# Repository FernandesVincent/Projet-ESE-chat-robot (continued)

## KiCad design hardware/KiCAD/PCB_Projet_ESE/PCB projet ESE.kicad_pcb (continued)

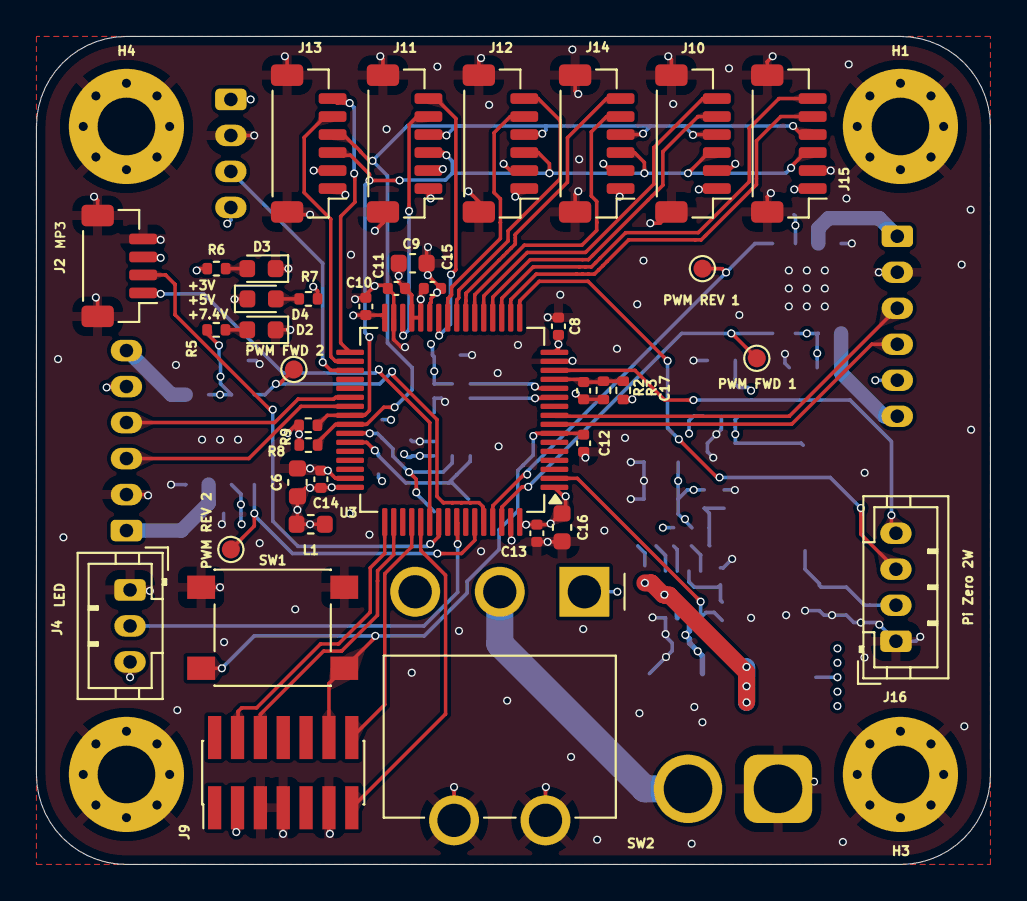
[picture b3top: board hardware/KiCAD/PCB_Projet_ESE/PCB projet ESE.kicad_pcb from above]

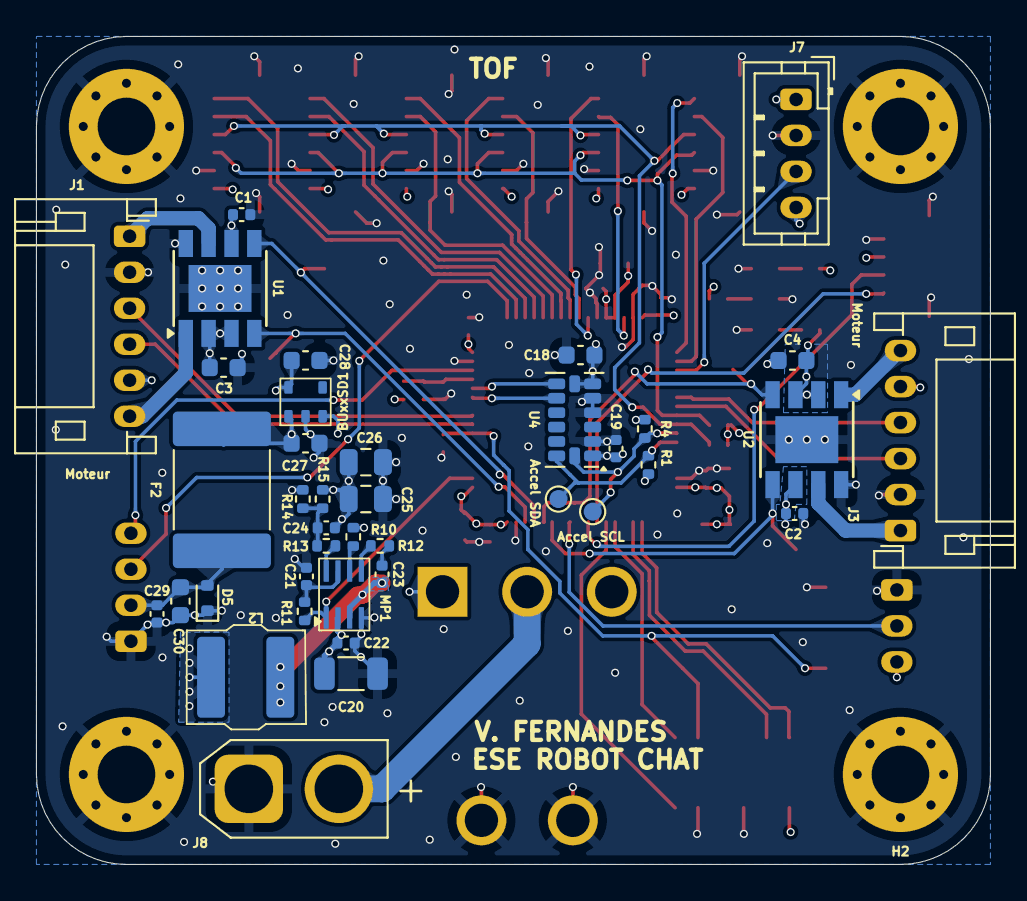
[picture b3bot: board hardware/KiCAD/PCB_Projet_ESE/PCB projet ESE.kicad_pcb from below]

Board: 4 copper layers, 53.0 x 46.0 mm, 82 parts (40 on the bottom side), 59 nets.

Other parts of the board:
Accel SCL: TestPoint; TestPoint_Pad_D1.0mm
Accel SDA: TestPoint; TestPoint_Pad_D1.0mm
PWM FWD 1, PWM FWD 2: TestPoint; TestPoint_Pad_D1.0mm
PWM REV 1, PWM REV 2: TestPoint; TestPoint_Pad_D1.0mm

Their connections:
Accel SCL: Accel SCL.1; also elsewhere on the board
Accel SDA: Accel SDA.1; also elsewhere on the board
PWM FWD 1: PWM FWD 1.1; also elsewhere on the board
PWM FWD 2: PWM FWD 2.1; also elsewhere on the board
PWM REV 1: PWM REV 1.1; also elsewhere on the board
PWM REV 2: PWM REV 2.1; also elsewhere on the board

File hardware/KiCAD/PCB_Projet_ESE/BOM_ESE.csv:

'Reference';'Qty';'Value';'Footprint'
'BUxxSD1';'1';'~';'Régu:SSOP5_BUxxSD5'
'C1,C2,C8,C10,C11,C12,C13,C14,C17,C19,C21,C22,C23,C29';'14';'100n';'Capacitor_SMD:C_0402_1005Metric'
'C3,C4,C6';'3';'4u7';'Capacitor_SMD:C_0603_1608Metric'
'C9,C16,C18,C27,C28';'5';'1u';'Capacitor_SMD:C_0603_1608Metric'
'C15';'1';'10n';'Capacitor_SMD:C_0402_1005Metric'
'C20';'1';'22u';'Capacitor_SMD:C_1206_3216Metric'
'C24';'1';'15p';'Capacitor_SMD:C_0402_1005Metric'
'C25,C26';'2';'22u';'Capacitor_SMD:C_0805_2012Metric'
'C30';'1';'10u';'Capacitor_SMD:C_0603_1608Metric'
'D2,D3,D4';'3';'LED';'LED_SMD:LED_0603_1608Metric'
'D5';'1';'D_TVS_Small';'Diode_SMD:D_SOD-523'
'F2';'1';'1A';'Fuse:Fuse_2920_7451Metric'
'H1,H2,H3,H4';'4';'MountingHole_Pad';'MountingHole:MountingHole_3.2mm_M3_Pad_Via'
'J1,J3';'2';'Conn_01x06';'Connector_JST:JST_PH_S6B-PH-K_1x06_P2.00mm_Horizontal'
'J2';'1';'Conn_01x04';'Connector_JST:JST_SH_BM04B-SRSS-TB_1x04-1MP_P1.00mm_Vertical'
'J4';'1';'Conn_01x03';'Connector_JST:JST_PH_B3B-PH-K_1x03_P2.00mm_Vertical'
'J7,J16';'2';'Conn_01x04';'Connector_JST:JST_PH_B4B-PH-K_1x04_P2.00mm_Vertical'
'J8';'1';'Conn_01x02';'Connector_AMASS:AMASS_XT30U-M_1x02_P5.0mm_Vertical'
'J9';'1';'Conn_ST_STDC14';'Connector_PinHeader_1.27mm:PinHeader_2x07_P1.27mm_Vertical_SMD'
'J10,J11,J12,J13,J14,J15';'6';'Conn_01x06';'Connector_JST:JST_SH_BM06B-SRSS-TB_1x06-1MP_P1.00mm_Vertical'
'L1';'1';'39n';'Inductor_SMD:L_0603_1608Metric'
'L2';'1';'4u7';'Régu:74404054068'
'MP1';'1';'~';'Régu:TSOT23-8'
'R1,R4,R8,R9';'4';'1k';'Resistor_SMD:R_0402_1005Metric'
'R2';'1';'20k';'Resistor_SMD:R_0402_1005Metric'
'R3';'1';'5k6';'Resistor_SMD:R_0402_1005Metric'
'R5';'1';'2k9';'Resistor_SMD:R_0402_1005Metric'
'R6';'1';'1k65';'Resistor_SMD:R_0402_1005Metric'
'R7';'1';'800';'Resistor_SMD:R_0402_1005Metric'
'R10,R11';'2';'100k';'Resistor_SMD:R_0402_1005Metric'
'R12';'1';'20';'Resistor_SMD:R_0402_1005Metric'
'R13';'1';'16k';'Resistor_SMD:R_0402_1005Metric'
'R14';'1';'7k68';'Resistor_SMD:R_0402_1005Metric'
'R15';'1';'40k2';'Resistor_SMD:R_0402_1005Metric'
'SW1';'1';'SW_SPST';'Régu:SW_SPST'
'SW2';'1';'472121010111';'Régu:SW_Wurth_WS-TOTV_472123020421'
'TP1,TP2,TP3,TP4,TP5,TP6';'6';'TestPoint';'TestPoint:TestPoint_Pad_D1.0mm'
'U1,U2';'2';'ZXBM5210-SP';'Package_SO:Diodes_SO-8EP'
'U3';'1';'STM32G474RETx';'Package_QFP:LQFP-64_10x10mm_P0.5mm'
'U4';'1';'ADXL343';'Package_LGA:LGA-14_3x5mm_P0.8mm_LayoutBorder1x6y'

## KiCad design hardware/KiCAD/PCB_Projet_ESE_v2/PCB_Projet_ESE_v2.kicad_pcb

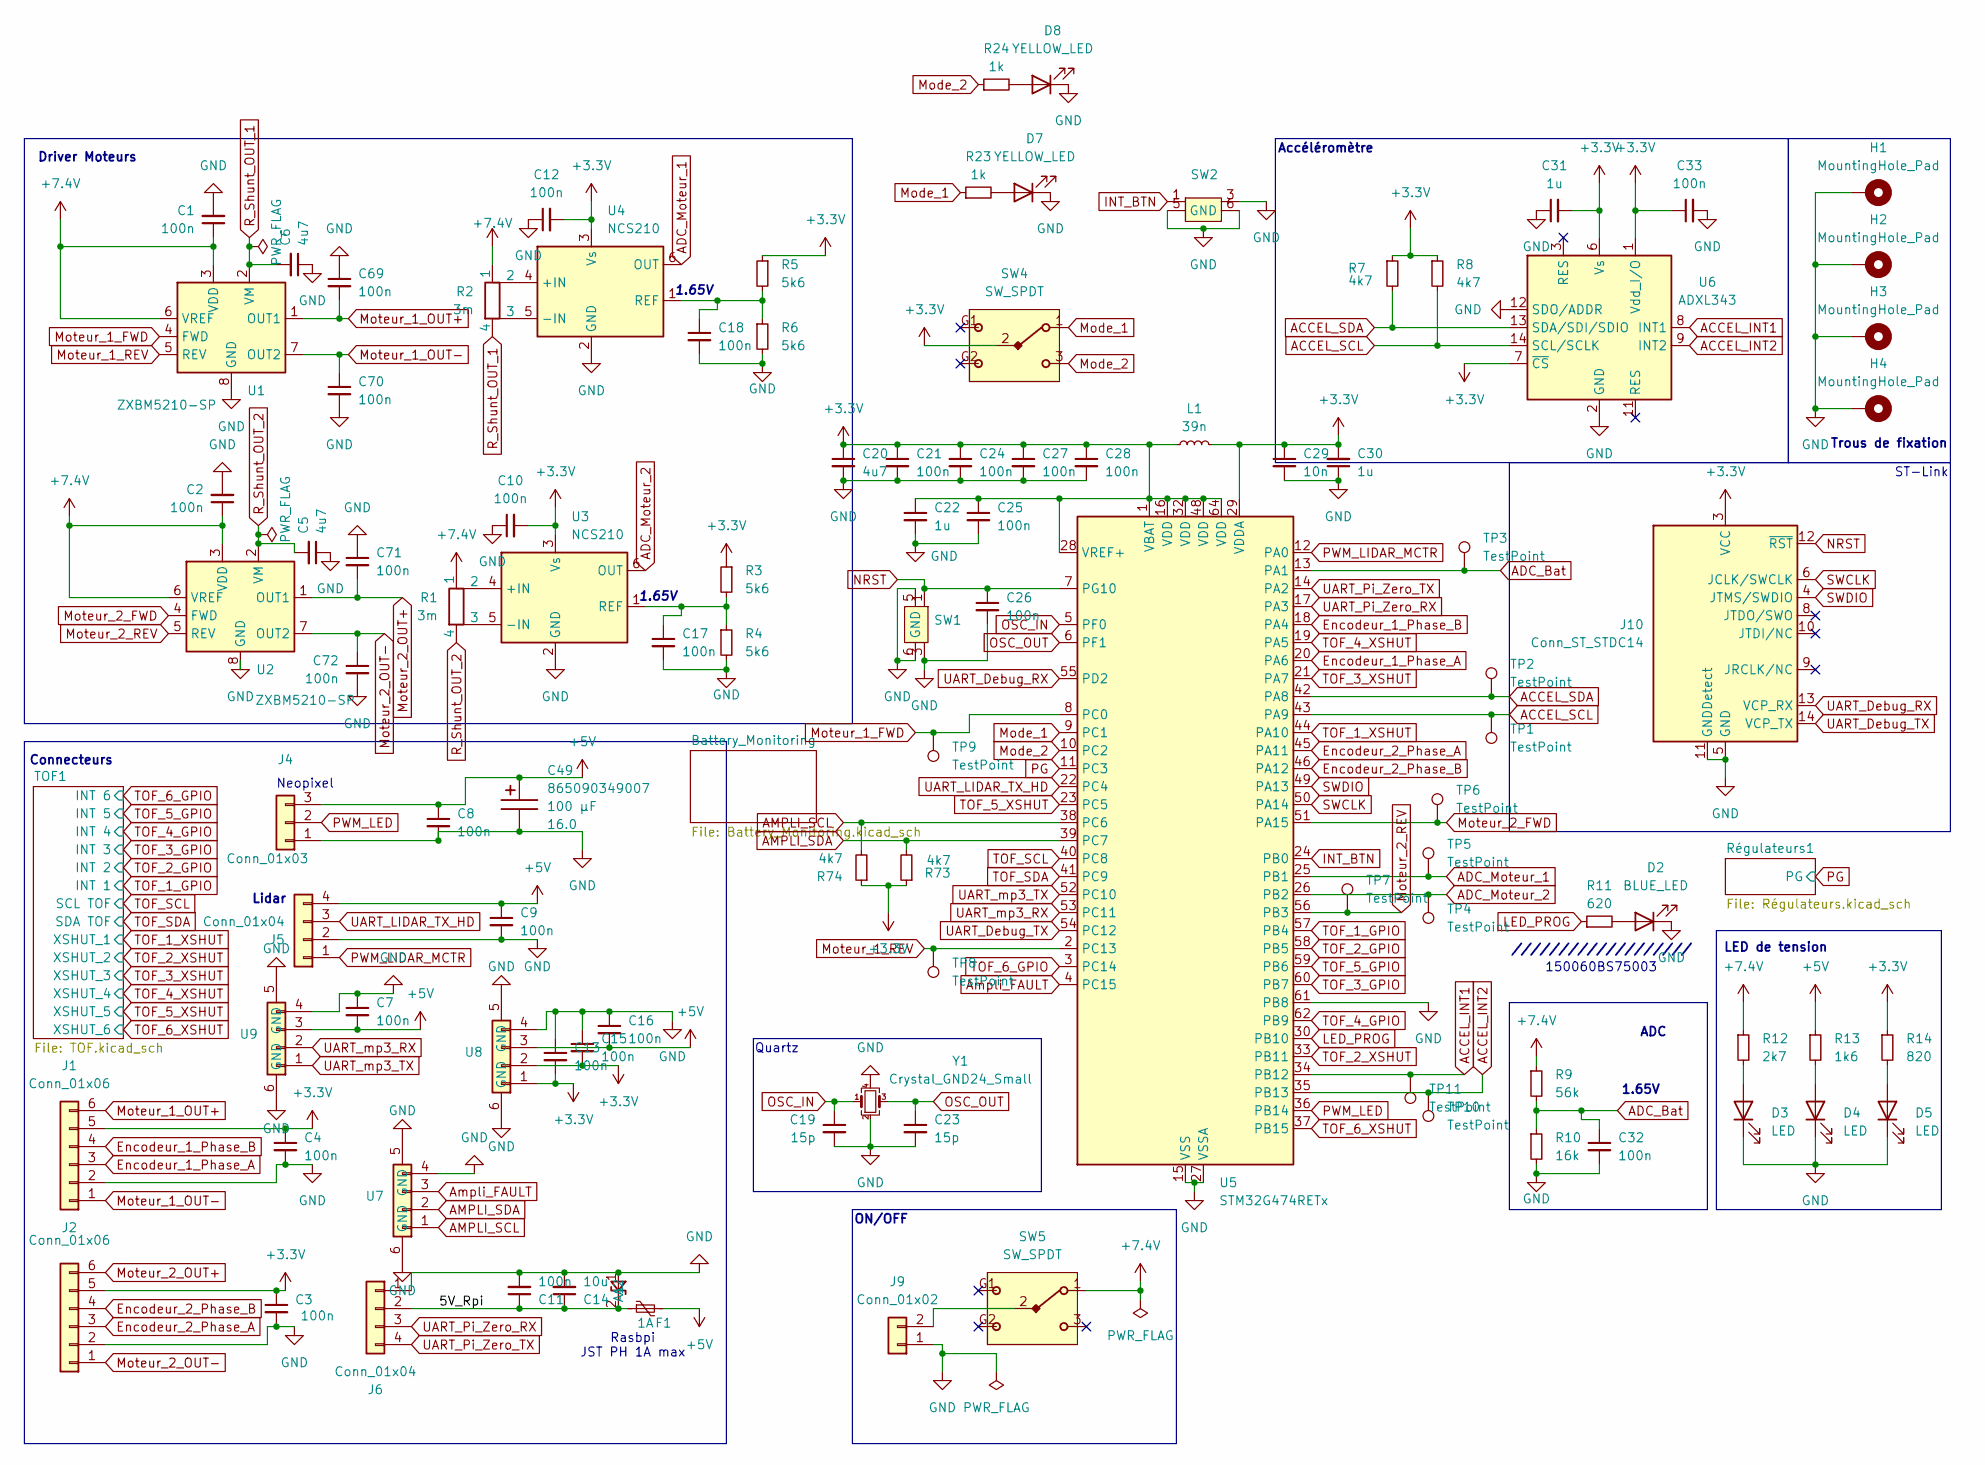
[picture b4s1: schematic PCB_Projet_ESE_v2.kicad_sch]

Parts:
C1, C2, C3, C4, C7, C8, C9, C10, C11, C12, C13, C15, C16, C17, C18, C21, C24, C25, C26, C27, C28, C32, C33, C69, C70, C71, C72: 100n; C_0402_1005Metric
C5, C6, C20: 4u7; C_0603_1608Metric
C14: 10u; C_0603_1608Metric
C19, C23: 15p; C_0603_1608Metric
C22, C30, C31: 1u; C_0402_1005Metric
C29: 10n; C_0402_1005Metric
C49: D8L6.5_865090349007; CP_Wurth_WCAP-ASLU-D8L6.5; Voltage 16.0; Part Number 865090349007
D2: BLUE_LED; LED_0603_1608Metric; MPN VLMB1501-GS08
D3, D4, D5: LED; LED_0603_1608Metric
D7, D8: YELLOW_LED; wurth_155060YS75300; MPN 155060YS75300
D20: D_SOD-523
F1: 1A; Fuse_2920_7451Metric; MPN 0ZAF0013FF28
H1, H2, H3, H4: MountingHole_Pad; Pad_traversant_M1
J1, J2: Conn_01x06; JST_PH_S6B-PH-K_1x06_P2.00mm_Horizontal
J4: Conn_01x03; JST_PH_B3B-PH-K_1x03_P2.00mm_Vertical
J5, J6: Conn_01x04; J_Wurth_WR-WTB_62000411722
J9: Conn_01x02; AMASS_XT30U-M_1x02_P5.0mm_Vertical
J10: Conn_ST_STDC14; PinHeader_2x07_P1.27mm_Vertical_SMD; MPN STLINK-V3MINIE
L1: 39n; L_0603_1608Metric
R1, R2: 3m; R_Shunt_Vishay_WSK2512_6332Metric_T2.21mm; MPN WSK25123L000DEA
R3, R4, R5, R6: 5k6; R_0402_1005Metric
R7, R8, R73, R74: 4k7; R_0402_1005Metric
R9: 56k; R_0402_1005Metric
R10: 16k; R_0402_1005Metric
R11: 620; R_0402_1005Metric
R12: 2k7; R_0402_1005Metric
R13: 1k6; R_0402_1005Metric
R14: 820; R_0402_1005Metric
R23, R24: 1k; R_0402_1005Metric
SW1, SW2: WS-TASV SMT Tact Switch 3.0 x 2.6 mm
SW4, SW5: SW_SPDT; SW_Wurth_WS-TOTV_472123020421; Part Number 472121010111
TP1, TP2, TP3, TP4, TP5, TP6, TP7, TP8, TP9, TP10, TP11: TestPoint; TestPoint_Pad_D1.0mm
U1, U2: ZXBM5210-SP; Diodes_SO-8EP; MPN ZXBM5210-SP-13
U3, U4: NCS210; SOT-363_SC-70-6
U5: STM32G474RETx; LQFP-64_10x10mm_P0.5mm
U6: ADXL343; LGA-14_3x5mm_P0.8mm_LayoutBorder1x6y; MPN ADXL343BCCZ-RL
U7, U8, U9: Wurth_Vertical_4_pos_0.8mm
Y1: Crystal_GND24_Small; Crystal_SMD_3225-4Pin_3.2x2.5mm; MPN Farnell : 2853935

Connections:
+3.3V: C3.1, C4.1, C10.2, C12.2, C13.2, C15.2, C20.1, C21.1, C22.1, C24.1, C25.1, C27.1, C28.1, C29.1, C30.2, C31.2, C33.1, J1.5, J2.5, J10.3 (VCC), L1.1, L1.2, R3.1, R5.1, R7.1, R8.1, R14.1, R73.1, R74.1, SW4.2, U3.3 (Vs), U4.3 (Vs), U5.1 (VBAT), U5.16 (VDD), U5.28 (VREF+), U5.29 (VDDA), U5.32 (VDD), U5.48 (VDD), U5.64 (VDD), U6.1 (Vdd_I/O), U6.6 (Vs), U6.7 (~CS), U8.1, U8.2; also elsewhere on the board
+5V: C7.2, C8.1, C9.1, C16.2, C49.1, F1.2, J4.3, J5.4, R13.1, U8.3, U9.3; also elsewhere on the board
+7.4V: C1.1, C2.1, R1.1, R2.1, R9.1, R12.1, SW5.1, U1.3 (VDD), U1.6 (VREF), U2.3 (VDD), U2.6 (VREF); also elsewhere on the board
/5V_Rpi: C11.1, C14.1, D20.2 (A2), F1.1, J6.2
ACCEL_INT1: TP11.1, U5.34 (PB12), U6.8 (INT1)
ACCEL_INT2: TP10.1, U5.35 (PB13), U6.9 (INT2)
ACCEL_SCL: R8.2, TP1.1, U5.43 (PA9), U6.14 (SCL/SCLK)
ACCEL_SDA: R7.2, TP2.1, U5.42 (PA8), U6.13 (SDA/SDI/SDIO)
ADC_Bat: C32.1, R9.2, R10.1, TP3.1, U5.13 (PA1)
ADC_Moteur_1: TP5.1, U4.6 (OUT), U5.25 (PB1)
ADC_Moteur_2: TP4.1, U3.6 (OUT), U5.26 (PB2)
AMPLI_SCL: R74.2, U5.38 (PC6), U7.1
AMPLI_SDA: R73.2, U5.39 (PC7), U7.2
Ampli_FAULT: U5.4 (PC15), U7.3
Encodeur_1_Phase_A: J1.3, U5.20 (PA6)
Encodeur_1_Phase_B: J1.4, U5.18 (PA4)
Encodeur_2_Phase_A: J2.3, U5.45 (PA11)
Encodeur_2_Phase_B: J2.4, U5.46 (PA12)
GND: C1.2, C2.2, C3.2, C4.2, C5.1, C6.1, C7.1, C8.2, C9.2, C10.1, C11.2, C12.1, C13.1, C14.2, C15.1, C16.1, C17.2, C18.2, C19.2, C20.2, C21.2, C22.2, C23.2, C24.2, C25.2, C26.2, C27.2, C28.2, C29.2, C30.1, C31.1, C32.2, C33.2, C49.2, C69.1, C70.2, C71.1, C72.2, D2.1 (K), D3.1 (K), D4.1 (K), D5.1 (K), D7.1 (K), D8.1 (K), D20.1 (A1), H1.1, H2.1, H3.1, H4.1, J1.2, J2.2, J4.1, J5.2, J6.1, J9.1, J10.5 (GND), J10.7 (GND), J10.11 (GNDDetect), R4.2, R6.2, R10.2, SW1.3, SW1.4, SW1.5, SW1.6 (GND), SW2.3, SW2.4, SW2.5, SW2.6 (GND), U1.8 (GND), U1.9 (GND), U2.8 (GND), U2.9 (GND), U3.2 (GND), U4.2 (GND), U5.15 (VSS), U5.27 (VSSA), U5.31 (VSS), U5.47 (VSS), U5.61 (PB8), U5.63 (VSS), U6.2 (GND), U6.4 (GND), U6.5 (GND), U6.12 (SDO/ADDR), U7.4, U7.5 (GND), U7.6 (GND), U8.4, U8.5 (GND), U8.6 (GND), U9.4, U9.5 (GND), U9.6 (GND), Y1.2, Y1.4; also elsewhere on the board
INT_BTN: SW2.1, SW2.2, U5.24 (PB0)
LED_PROG: R11.1, U5.30 (PB10)
Mode_1: R23.1, SW4.1, U5.9 (PC1)
Mode_2: R24.1, SW4.3, U5.10 (PC2)
Moteur_1_FWD: TP9.1, U1.4 (FWD), U5.8 (PC0)
Moteur_1_OUT+: C69.2, J1.6, U1.1 (OUT1)
Moteur_1_OUT-: C70.1, J1.1, U1.7 (OUT2)
Moteur_1_REV: TP8.1, U1.5 (REV), U5.2 (PC13)
Moteur_2_FWD: TP6.1, U2.4 (FWD), U5.51 (PA15)
Moteur_2_OUT+: C71.2, J2.6, U2.1 (OUT1)
Moteur_2_OUT-: C72.1, J2.1, U2.7 (OUT2)
Moteur_2_REV: TP7.1, U2.5 (REV), U5.56 (PB3)
NRST: C26.1, J10.12 (~RST), SW1.1, SW1.2, U5.7 (PG10)
unnamed: D2.2 (A), R11.2
unnamed: D3.2 (A), R12.2
unnamed: D4.2 (A), R13.2
unnamed: D5.2 (A), R14.2
unnamed: D7.2 (A), R23.2
unnamed: D8.2 (A), R24.2
unnamed: J9.2, SW5.2
unnamed: R1.2, U3.4 (+IN)
unnamed: R1.3, U3.5 (-IN)
unnamed: C17.1, R3.2, R4.1, U3.1 (REF)
unnamed: R2.2, U4.4 (+IN)
unnamed: R2.3, U4.5 (-IN)
unnamed: C18.1, R5.2, R6.1, U4.1 (REF)
OSC_IN: C19.1, U5.5 (PF0), Y1.1
OSC_OUT: C23.1, U5.6 (PF1), Y1.3
PG: U5.11 (PC3); also elsewhere on the board
PWM_LED: J4.2, U5.36 (PB14)
PWM_LIDAR_MCTR: J5.1, U5.12 (PA0)
R_Shunt_OUT_1: C6.2, R2.4, U1.2 (VM)
R_Shunt_OUT_2: C5.2, R1.4, U2.2 (VM)
SWCLK: J10.6 (JCLK/SWCLK), U5.50 (PA14)
SWDIO: J10.4 (JTMS/SWDIO), U5.49 (PA13)
TOF_1_GPIO: U5.57 (PB4); also elsewhere on the board
TOF_1_XSHUT: U5.44 (PA10); also elsewhere on the board
TOF_2_GPIO: U5.58 (PB5); also elsewhere on the board
TOF_2_XSHUT: U5.33 (PB11); also elsewhere on the board
TOF_3_GPIO: U5.60 (PB7); also elsewhere on the board
TOF_3_XSHUT: U5.21 (PA7); also elsewhere on the board
TOF_4_GPIO: U5.62 (PB9); also elsewhere on the board
TOF_4_XSHUT: U5.19 (PA5); also elsewhere on the board
TOF_5_GPIO: U5.59 (PB6); also elsewhere on the board
TOF_5_XSHUT: U5.23 (PC5); also elsewhere on the board
TOF_6_GPIO: U5.3 (PC14); also elsewhere on the board
TOF_6_XSHUT: U5.37 (PB15); also elsewhere on the board
TOF_SCL: U5.40 (PC8); also elsewhere on the board
TOF_SDA: U5.41 (PC9); also elsewhere on the board
UART_Debug_RX: J10.13 (VCP_RX), U5.55 (PD2)
UART_Debug_TX: J10.14 (VCP_TX), U5.54 (PC12)
UART_LIDAR_TX_HD: J5.3, U5.22 (PC4)
UART_Pi_Zero_RX: J6.3, U5.17 (PA3)
UART_Pi_Zero_TX: J6.4, U5.14 (PA2)
UART_mp3_RX: U5.53 (PC11), U9.2
UART_mp3_TX: U5.52 (PC10), U9.1

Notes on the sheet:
Rasbpi JST PH 1A max
ST-Link
ON/OFF
LED de tension
Driver Moteurs
Lidar
Connecteurs
Neopixel
Accéléromètre
Quartz
ADC
///////////////////
1.65V
Trous de fixation
150060BS75003

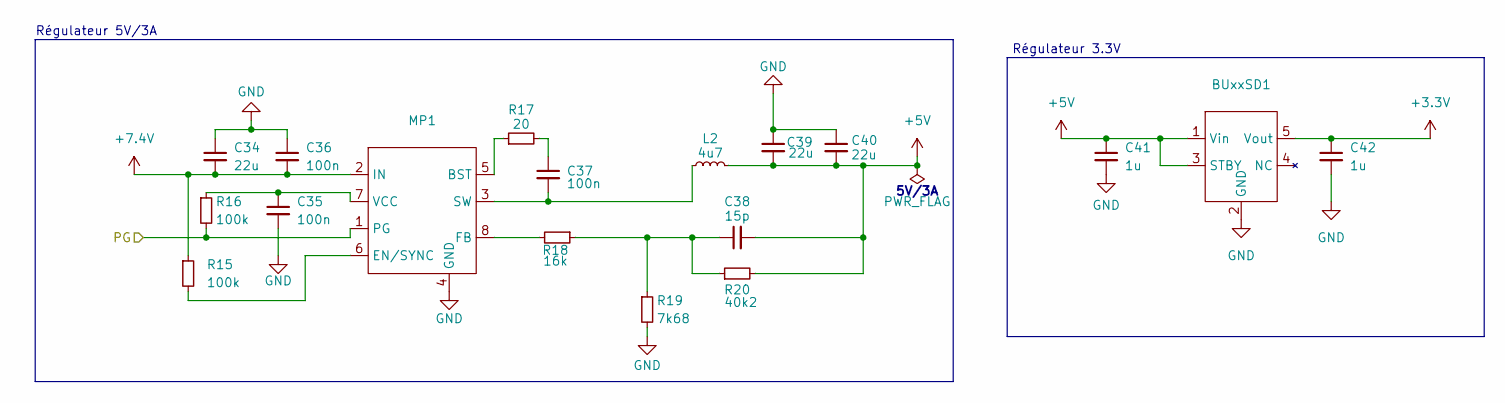
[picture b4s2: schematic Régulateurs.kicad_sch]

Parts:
BUxxSD1: SSOP5_BUxxSD5; MPN BU33SD5WG-TR
C34: 22u; C_1206_3216Metric
C35, C36, C37: 100n; C_0402_1005Metric
C38: 15p; C_0402_1005Metric
C39, C40: 22u; C_0805_2012Metric
C41, C42: 1u; C_0402_1005Metric
L2: 4u7; 74404054068
MP1: TSOT23-8; MPN MP1475DJ-LF-P
R15, R16: 100k; R_0402_1005Metric
R17: 20; R_0402_1005Metric
R18: 16k; R_0402_1005Metric
R19: 7k68; R_0402_1005Metric
R20: 40k2; R_0402_1005Metric

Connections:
+3.3V: BUxxSD1.5 (Vout), C42.1; also elsewhere on the board
+5V: BUxxSD1.1 (Vin), BUxxSD1.3 (STBY), C38.2, C39.2, C40.2, C41.1, L2.2, R20.2; also elsewhere on the board
+7.4V: C34.2, C36.2, MP1.2 (IN), R15.1; also elsewhere on the board
GND: BUxxSD1.2 (GND), C34.1, C35.2, C36.1, C39.1, C40.1, C41.2, C42.2, MP1.4 (GND), R19.2; also elsewhere on the board
unnamed: C37.1, R17.2
unnamed: C38.1, R18.1, R19.1, R20.1
unnamed: MP1.5 (BST), R17.1
unnamed: MP1.6 (EN/SYNC), R15.2
unnamed: MP1.8 (FB), R18.2
unnamed: C37.2, L2.1, MP1.3 (SW)
unnamed: C35.1, MP1.7 (VCC), R16.1
PG: MP1.1 (PG), R16.2; also elsewhere on the board

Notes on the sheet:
Régulateur 3.3V
5V/3A
Régulateur 5V/3A

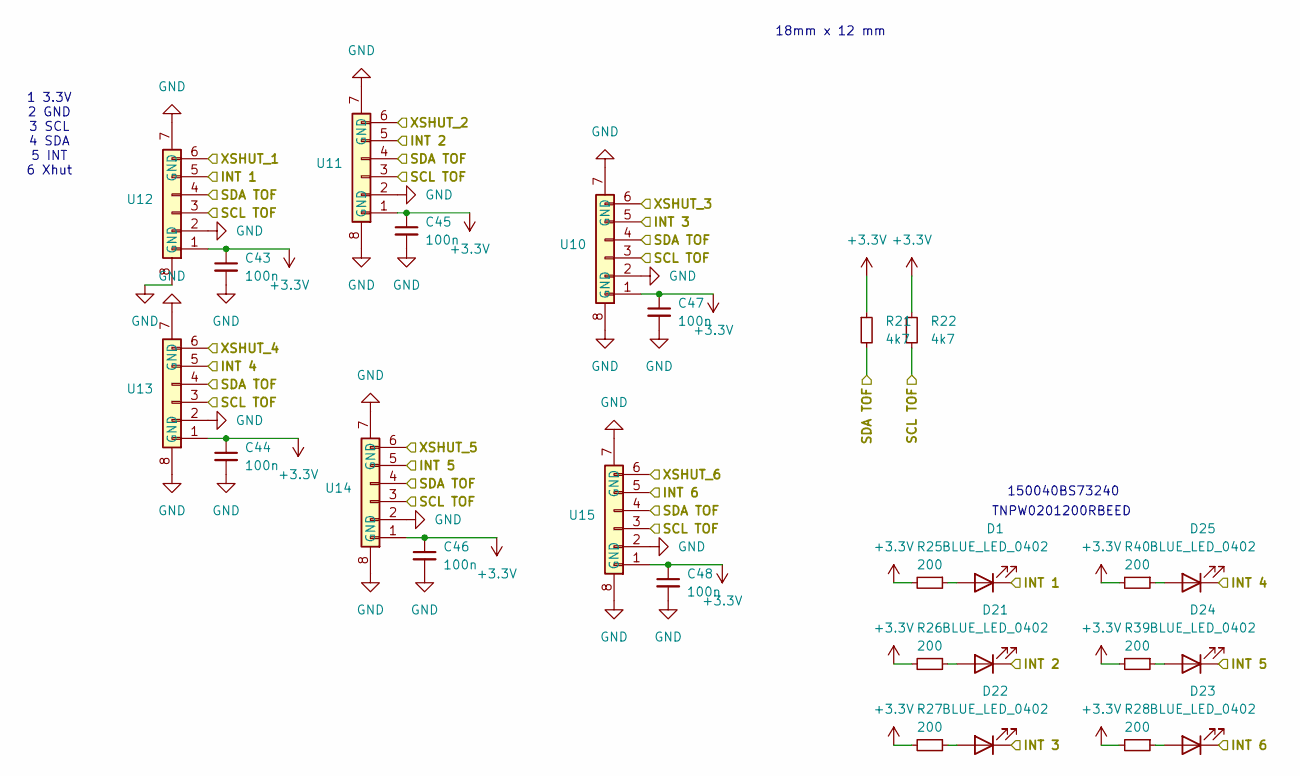
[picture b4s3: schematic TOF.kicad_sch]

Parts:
C43, C44, C45, C46, C47, C48: 100n; C_0402_1005Metric
D1, D21, D22, D23, D24, D25: BLUE_LED_0402; LED_0402_1005Metric
R21, R22: 4k7; R_0402_1005Metric
R25, R26, R27, R28, R39, R40: 200; R_0201_0603Metric
U10, U11, U12, U13, U14, U15: Wurth_Vertical_6_pos_0.8mm

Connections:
+3.3V: C43.1, C44.1, C45.1, C46.1, C47.1, C48.1, R21.1, R22.1, R25.2, R26.2, R27.2, R28.2, R39.2, R40.2, U10.1, U11.1, U12.1, U13.1, U14.1, U15.1; also elsewhere on the board
GND: C43.2, C44.2, C45.2, C46.2, C47.2, C48.2, U10.2, U10.7 (GND), U10.8 (GND), U11.2, U11.7 (GND), U11.8 (GND), U12.2, U12.7 (GND), U12.8 (GND), U13.2, U13.7 (GND), U13.8 (GND), U14.2, U14.7 (GND), U14.8 (GND), U15.2, U15.7 (GND), U15.8 (GND); also elsewhere on the board
unnamed: D1.2 (A), R25.1
unnamed: D21.2 (A), R26.1
unnamed: D22.2 (A), R27.1
unnamed: D23.2 (A), R28.1
unnamed: D24.2 (A), R39.1
unnamed: D25.2 (A), R40.1
TOF_1_GPIO: D1.1 (K), U12.5; also elsewhere on the board
TOF_1_XSHUT: U12.6; also elsewhere on the board
TOF_2_GPIO: D21.1 (K), U11.5; also elsewhere on the board
TOF_2_XSHUT: U11.6; also elsewhere on the board
TOF_3_GPIO: D22.1 (K), U10.5; also elsewhere on the board
TOF_3_XSHUT: U10.6; also elsewhere on the board
TOF_4_GPIO: D25.1 (K), U13.5; also elsewhere on the board
TOF_4_XSHUT: U13.6; also elsewhere on the board
TOF_5_GPIO: D24.1 (K), U14.5; also elsewhere on the board
TOF_5_XSHUT: U14.6; also elsewhere on the board
TOF_6_GPIO: D23.1 (K), U15.5; also elsewhere on the board
TOF_6_XSHUT: U15.6; also elsewhere on the board
TOF_SCL: R22.2, U10.3, U11.3, U12.3, U13.3, U14.3, U15.3; also elsewhere on the board
TOF_SDA: R21.2, U10.4, U11.4, U12.4, U13.4, U14.4, U15.4; also elsewhere on the board

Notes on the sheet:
18mm x 12 mm
150040BS73240
TNPW0201200RBEED
1 3.3V 2 GND 3 SCL 4 SDA 5 INT 6 Xhut

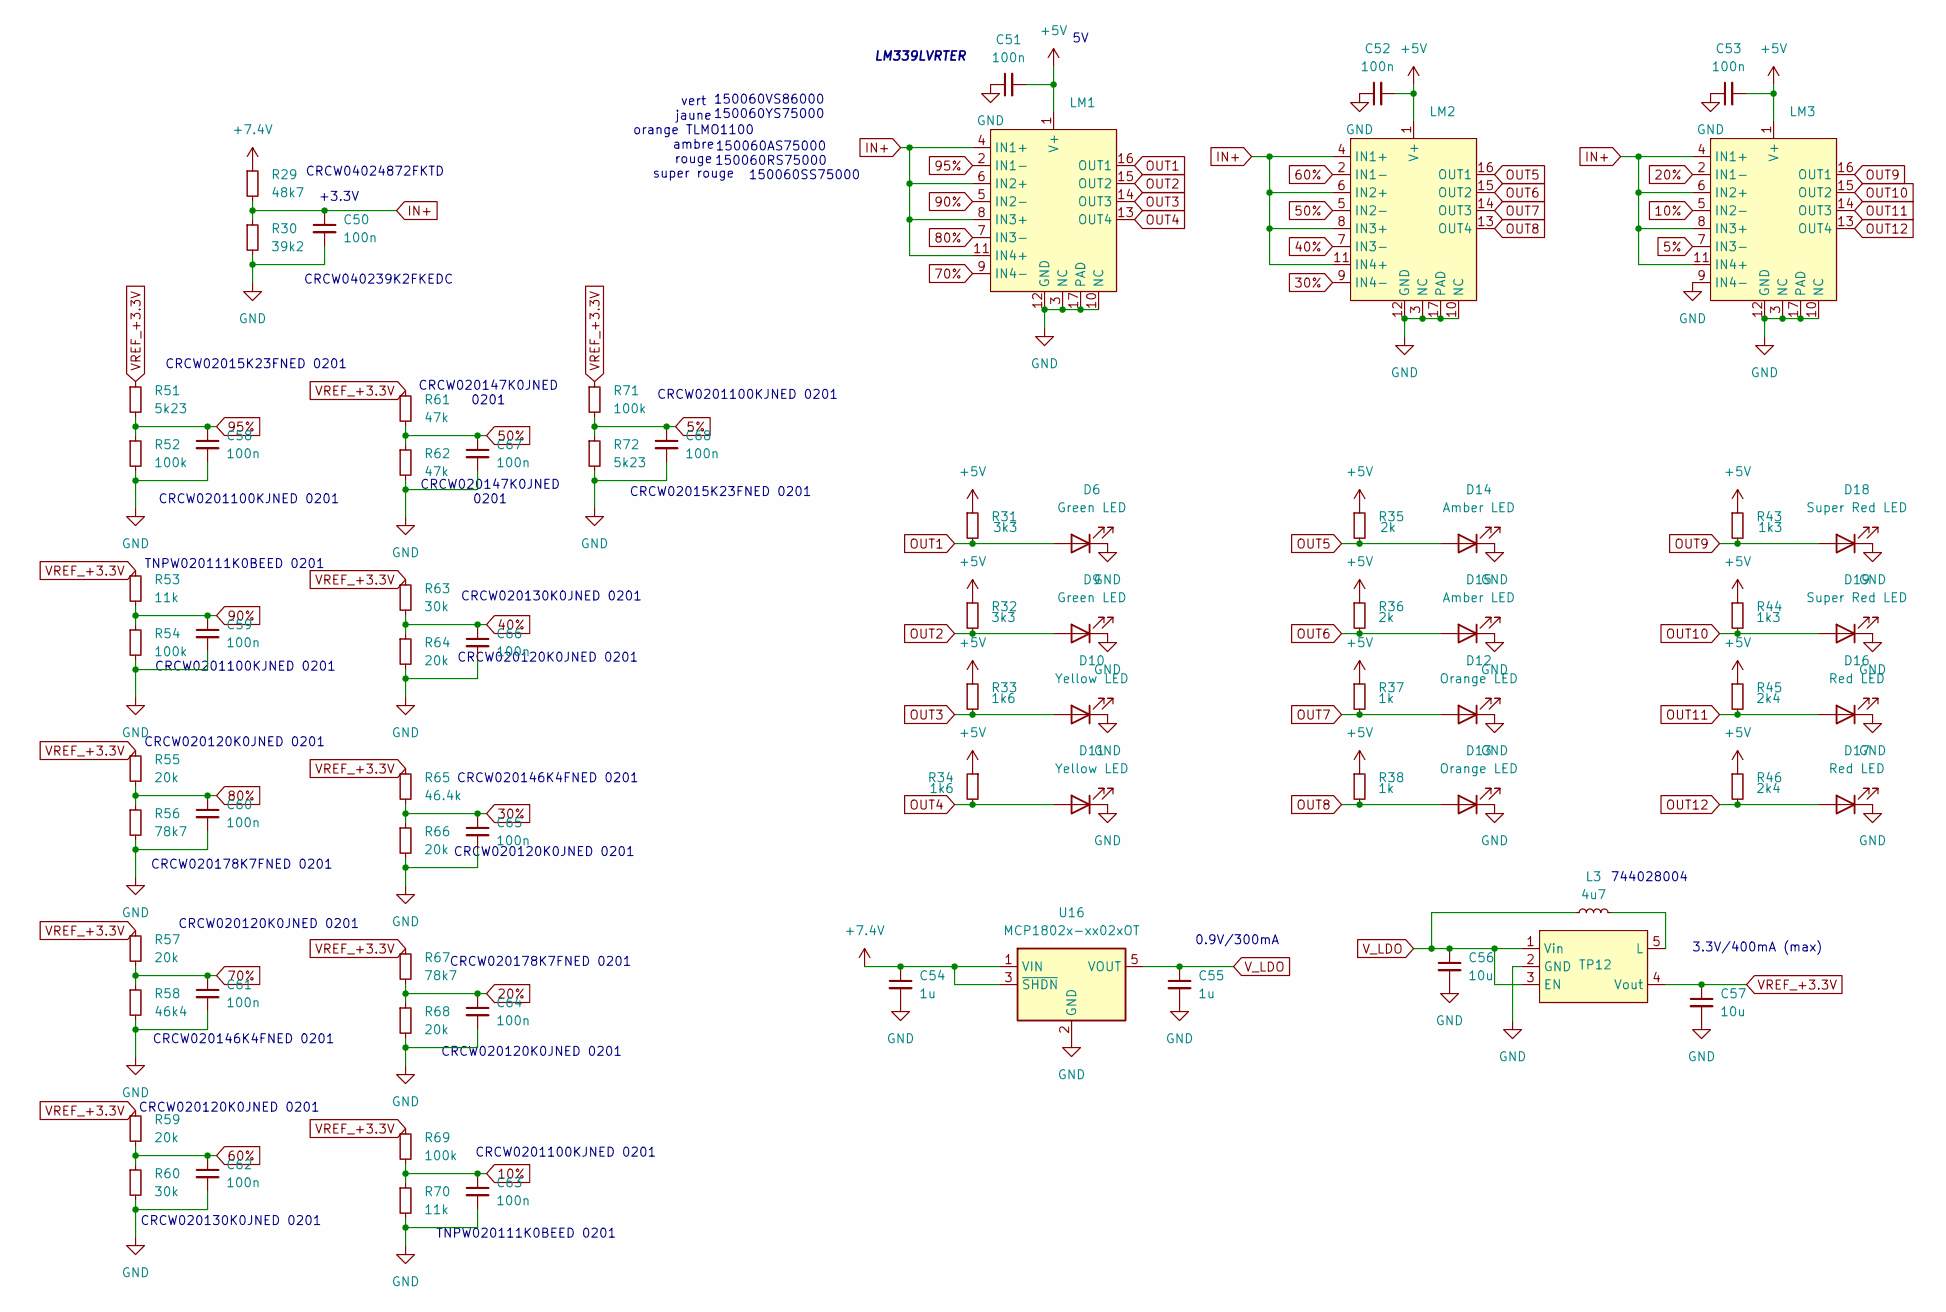
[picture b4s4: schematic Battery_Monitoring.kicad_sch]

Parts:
C50, C51, C52, C53, C58, C59, C60, C61, C62, C63, C64, C65, C66, C67, C68: 100n; C_0402_1005Metric
C54, C55: 1u; C_0402_1005Metric
C56, C57: 10u; C_0603_1608Metric
D6, D9: Green LED; LED_0603_1608Metric
D10, D11: Yellow LED; LED_0603_1608Metric
D12, D13: Orange LED; LED_0603_1608Metric
D14, D15: Amber LED; LED_0603_1608Metric
D16, D17: Red LED; LED_0603_1608Metric
D18, D19: Super Red LED; LED_0603_1608Metric
L3: 4u7; WE-TPC-744028004
LM1: WQFN-16-1EP_3x3mm_P0.5mm_EP1.68x1.68mm
LM2, LM3: WQFN-16-1EP_3x3mm_P0.5mm_EP1.68x1.68mm; MPN LM339LVRTER
R29: 48k7; R_0402_1005Metric
R30: 39k2; R_0402_1005Metric
R31, R32: 3k3; R_0402_1005Metric
R33, R34: 1k6; R_0402_1005Metric
R35, R36: 2k; R_0402_1005Metric
R37, R38: 1k; R_0402_1005Metric
R43, R44: 1k3; R_0402_1005Metric
R45, R46: 2k4; R_0402_1005Metric
R51: 5k23; R_0201_0603Metric
R52, R54, R69, R71: 100k; R_0201_0603Metric
R53, R70: 11k; R_0201_0603Metric
R55, R57, R59, R64, R66, R68: 20k; R_0201_0603Metric
R56, R67: 78k7; R_0201_0603Metric
R58: 46k4; R_0201_0603Metric
R60, R63: 30k; R_0201_0603Metric
R61, R62: 47k; R_0201_0603Metric
R65: 46.4k; R_0201_0603Metric
R72: 5k23; R_0402_1005Metric
TP12: SOT-23-5; MPN TPS61097A-33DBVR
U16: MCP1802x-xx02xOT; SOT-23-5; MPN MCP1802T-0902I/OT

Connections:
5%: C68.1, LM3.7 (IN3-), R71.2, R72.1
10%: C63.1, LM3.5 (IN2-), R69.2, R70.1
20%: C64.1, LM3.2 (IN1-), R67.2, R68.1
30%: C65.1, LM2.9 (IN4-), R65.2, R66.1
40%: C66.1, LM2.7 (IN3-), R63.2, R64.1
50%: C67.1, LM2.5 (IN2-), R61.2, R62.1
60%: C62.1, LM2.2 (IN1-), R59.2, R60.1
70%: C61.1, LM1.9 (IN4-), R57.2, R58.1
80%: C60.1, LM1.7 (IN3-), R55.2, R56.1
90%: C59.1, LM1.5 (IN2-), R53.2, R54.1
95%: C58.1, LM1.2 (IN1-), R51.2, R52.1
+5V: C51.2, C52.2, C53.2, LM1.1 (V+), LM2.1 (V+), LM3.1 (V+), R31.1, R32.1, R33.1, R34.1, R35.1, R36.1, R37.1, R38.1, R43.1, R44.1, R45.1, R46.1; also elsewhere on the board
+7.4V: C54.1, R29.1, U16.1 (VIN), U16.3 (~SHDN); also elsewhere on the board
GND: C50.2, C51.1, C52.1, C53.1, C54.2, C55.2, C56.2, C57.2, C58.2, C59.2, C60.2, C61.2, C62.2, C63.2, C64.2, C65.2, C66.2, C67.2, C68.2, D6.1 (K), D9.1 (K), D10.1 (K), D11.1 (K), D12.1 (K), D13.1 (K), D14.1 (K), D15.1 (K), D16.1 (K), D17.1 (K), D18.1 (K), D19.1 (K), LM1.3 (NC), LM1.10 (NC), LM1.12 (GND), LM1.17 (PAD), LM2.3 (NC), LM2.10 (NC), LM2.12 (GND), LM2.17 (PAD), LM3.3 (NC), LM3.9 (IN4-), LM3.10 (NC), LM3.12 (GND), LM3.17 (PAD), R30.2, R52.2, R54.2, R56.2, R58.2, R60.2, R62.2, R64.2, R66.2, R68.2, R70.2, R72.2, TP12.2 (GND), U16.2 (GND); also elsewhere on the board
IN+: C50.1, LM1.4 (IN1+), LM1.6 (IN2+), LM1.8 (IN3+), LM1.11 (IN4+), LM2.4 (IN1+), LM2.6 (IN2+), LM2.8 (IN3+), LM2.11 (IN4+), LM3.4 (IN1+), LM3.6 (IN2+), LM3.8 (IN3+), LM3.11 (IN4+), R29.2, R30.1
unnamed: L3.2, TP12.5 (L)
OUT1: D6.2 (A), LM1.16 (OUT1), R31.2
OUT2: D9.2 (A), LM1.15 (OUT2), R32.2
OUT3: D10.2 (A), LM1.14 (OUT3), R33.2
OUT4: D11.2 (A), LM1.13 (OUT4), R34.2
OUT5: D14.2 (A), LM2.16 (OUT1), R35.2
OUT6: D15.2 (A), LM2.15 (OUT2), R36.2
OUT7: D12.2 (A), LM2.14 (OUT3), R37.2
OUT8: D13.2 (A), LM2.13 (OUT4), R38.2
OUT9: D18.2 (A), LM3.16 (OUT1), R43.2
OUT10: D19.2 (A), LM3.15 (OUT2), R44.2
OUT11: D16.2 (A), LM3.14 (OUT3), R45.2
OUT12: D17.2 (A), LM3.13 (OUT4), R46.2
VREF_+3.3V: C57.1, R51.1, R53.1, R55.1, R57.1, R59.1, R61.1, R63.1, R65.1, R67.1, R69.1, R71.1, TP12.4 (Vout)
V_LDO: C55.1, C56.1, L3.1, TP12.1 (Vin), TP12.3 (EN), U16.5 (VOUT)

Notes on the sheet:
CRCW020147K0JNED 0201
TNPW020111K0BEED 0201
CRCW0201100KJNED 0201
CRCW04024872FKTD
vert jaune orange TLMO1100 ambre rouge super rouge
150060YS75000
CRCW020146K4FNED 0201
CRCW020120K0JNED 0201
CRCW020178K7FNED 0201
744028004
CRCW020130K0JNED 0201
+3.3V
CRCW02015K23FNED 0201
3.3V/400mA (max)
150060VS86000
150060AS75000
150060RS75000
CRCW040239K2FKEDC
150060SS75000
LM339LVRTER
0.9V/300mA

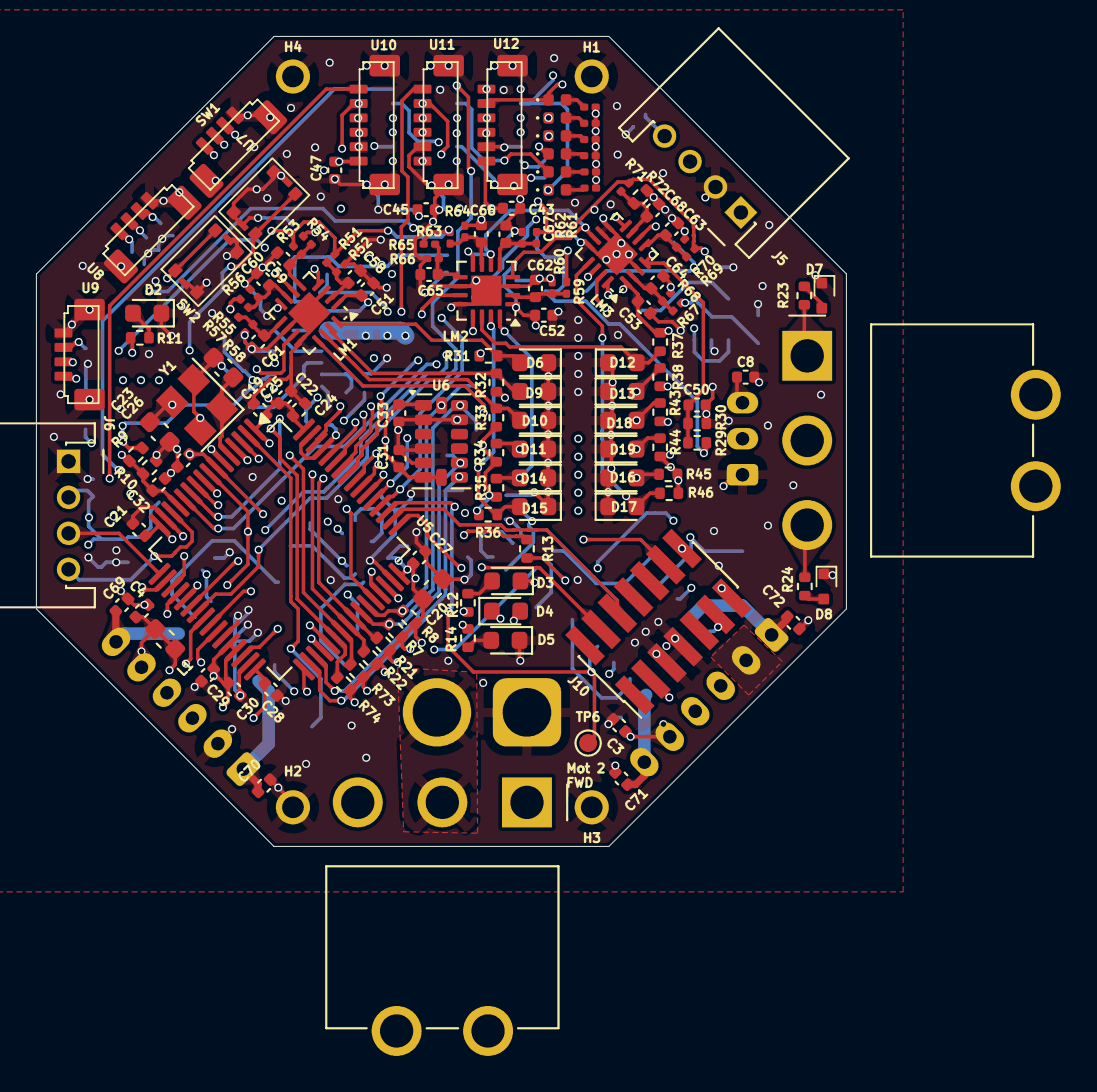
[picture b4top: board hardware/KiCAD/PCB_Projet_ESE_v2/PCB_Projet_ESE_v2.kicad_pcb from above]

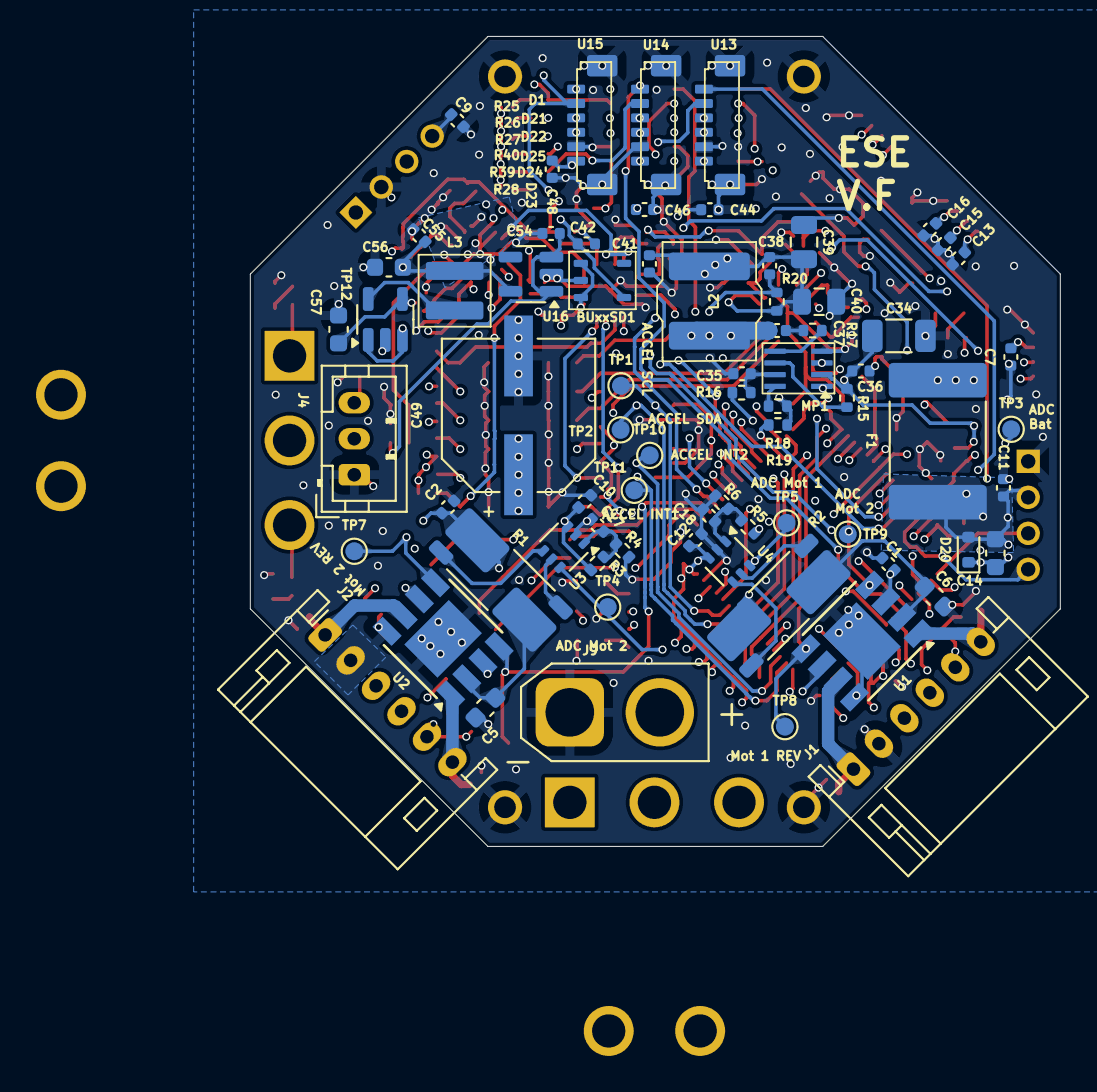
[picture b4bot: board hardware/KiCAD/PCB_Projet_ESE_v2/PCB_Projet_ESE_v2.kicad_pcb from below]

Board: 8 copper layers, 45.0 x 45.0 mm, 218 parts (73 on the bottom side), 115 nets.
